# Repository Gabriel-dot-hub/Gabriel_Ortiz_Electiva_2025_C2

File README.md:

# Gabriel_Ortiz_Electiva_2025_C2
Repositorio para las clases de la electiva con el profesor Carlos Antonio Pichardo Viuque

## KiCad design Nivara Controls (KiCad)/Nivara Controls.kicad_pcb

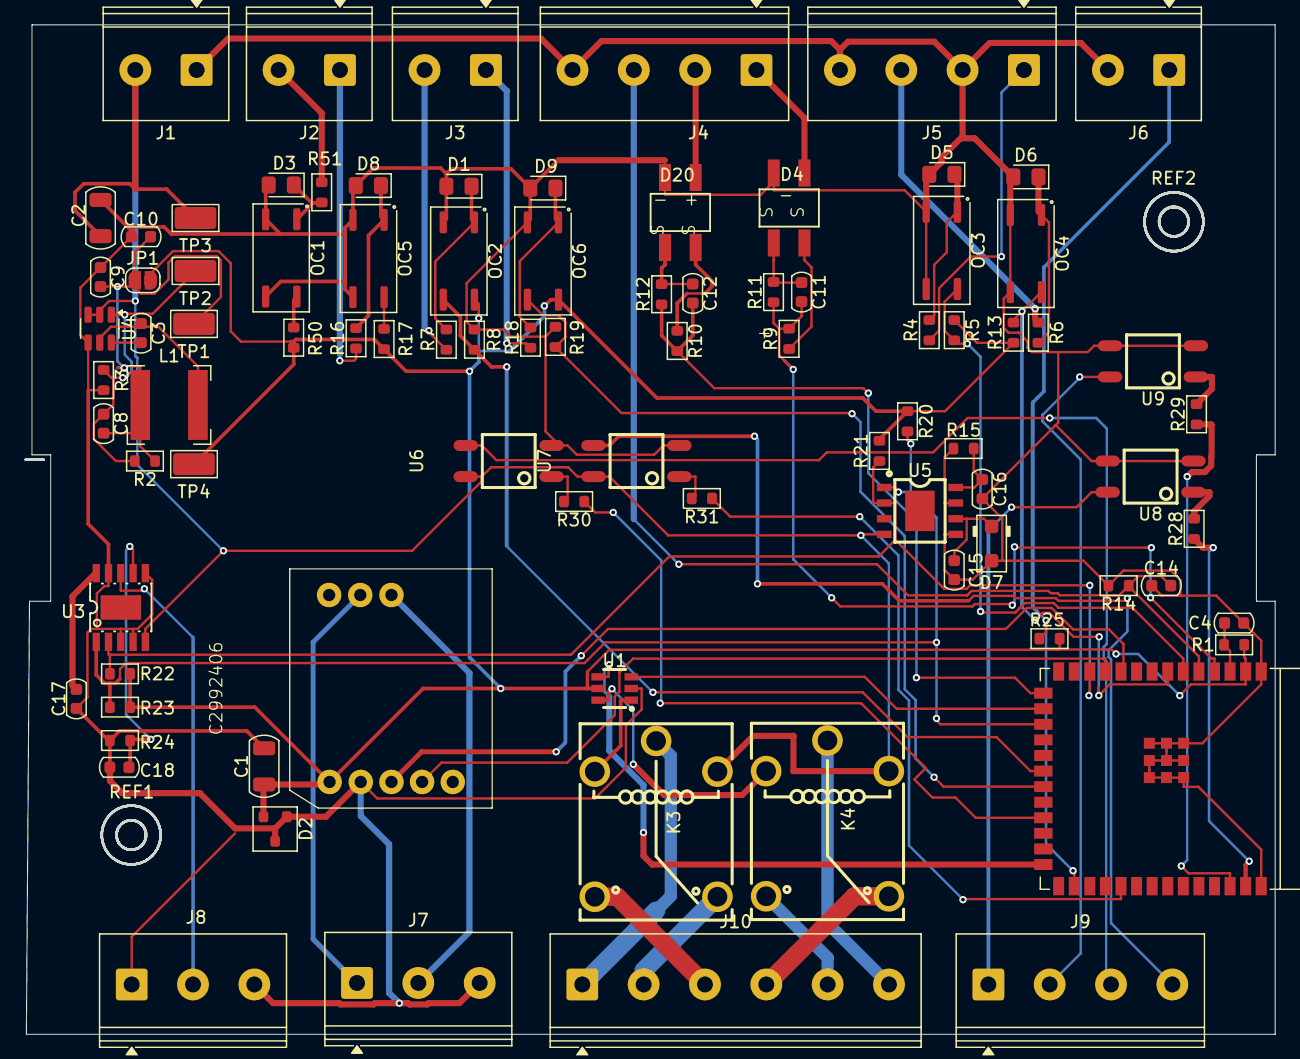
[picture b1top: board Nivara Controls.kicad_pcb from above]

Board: 2 copper layers, 101.8 x 82.3 mm, 91 parts (0 on the bottom side), 70 nets.

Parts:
C1, C2: C_1206; C_1206_3216Metric
C3, C4, C8, C9, C10, C11, C12, C14, C15, C16, C17, C18: C_0603; C_0603_1608Metric
C2992406: C2992406
D1, D3, D5, D6, D8, D9: DL4007; D_0805_2012Metric_Pad1.15x1.40mm_HandSolder
D2: SM712; SOT-23
D4, D20: MB24F_C7427849; MBF-SMD_L4.7-W3.8-P2.50-LS6.8-BL
D7: SMF24A; D_SOD-123F
J1, J2, J3, J6: Screw_Terminal_2_P5.00mm; TerminalBlock_Phoenix_PT-1,5-2-5.0-H_1x02_P5.00mm_Horizontal
J4, J5, J9: Screw_Terminal_4_P5.00mm; TerminalBlock_Phoenix_PT-1,5-4-5.0-H_1x04_P5.00mm_Horizontal
J7, J8: Screw_Terminal_3_P5.00mm; TerminalBlock_Phoenix_PT-1,5-3-5.0-H_1x03_P5.00mm_Horizontal
J10: Screw_Terminal_6_P5.00mm; TerminalBlock_Phoenix_PT-1,5-6-5.0-H_1x06_P5.00mm_Horizontal
JP1: SolderJumper_2_Open; SolderJumper-2_P1.3mm_Open_RoundedPad1.0x1.5mm
K3, K4: SRA-24VDC-CL; RELAY-TH_SRA-X-CX
L1: L_Iron; L_Bourns-SRN6028
OC1, OC2, OC3, OC4, OC5, OC6: LTV-357T-B; SO-4_4.4x3.9mm_P2.54mm
R1, R2, R3, R4, R5, R6, R7, R8, R9, R10, R11, R12, R13, R14, R15, R16, R17, R18, R19, R20, R21, R22, R23, R24, R25, R28, R29, R30, R31, R50, R51: R_0603; R_0603_1608Metric
REF1, REF2: MountingHole_2.5mm
TP1, TP2, TP3, TP4: TestPoint; TestPoint_Keystone_5015_Micro_Mini
U1: LK1802
U2: ESP32-S3-WROOM-1
U3: GP8303-TC50-EW; ESOP-10_L4.9-W3.9-P1.00-LS6.1-BL-EP
U4: AP63203WU; TSOT-23-6
U5: GP8201S-TC50-EW; GP8303-TC50-EW
U6, U7, U8, U9: GAQY211G2S; GAQY211G2s

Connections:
+3.3V: C1.1, C2992406.1 (VCC), D2.2 (A2), JP1.2 (B), OC2.4, OC6.4, R1.1, R5.1, R13.1, R17.1, R20.2, R21.2, R22.2, R23.2, R25.1, R50.1, TP4.1, U1.5 (COM), U2.2 (3V3)
/Board_NIVARA/0mA__10mA_module/SCLK: R20.1, R23.1, U2.17 (GPIO9/TOUCH9/ADC1_CH8/FSPIHD/SUBSPIHD), U3.1 (SLCK), U5.1 (SCLK)
/Board_NIVARA/0mA__10mA_module/SDA: R21.1, R22.1, U2.12 (GPIO8/TOUCH8/ADC1_CH7/SUBSPICS1), U3.2 (SDA), U5.2 (SDA)
/Board_NIVARA/0v__10v_Module/D_0v__10v: C11.2, R9.2, R11.1, U2.4 (GPIO4/TOUCH4/ADC1_CH3)
/Board_NIVARA/0v__32v__module/D_0v__32v__: C12.2, R10.2, R12.1, U2.15 (GPIO3/TOUCH3/ADC1_CH2)
/Board_NIVARA/+Digit_input_1_+: J5.1, R4.1
/Board_NIVARA/+Digit_input_2_+: J5.3, R6.1
/Board_NIVARA/Analog_0-10_input_1: D4.3 (C1), J4.1
/Board_NIVARA/Analog_0-32_input_1: D20.3 (C1), J4.2
/Board_NIVARA/Analog_0_10_OUT_1: C15.2, D7.1 (K), U5.6 (VOUT)
/Board_NIVARA/Analog_4-20_input_1: C14.2, J4.3, R14.1, U2.5 (GPIO5/TOUCH5/ADC1_CH4)
/Board_NIVARA/Analog_4_20_OUT_1: J8.2, U3.8 (IOUT)
/Board_NIVARA/Digit_module/Digit_input1_--: OC3.4, R5.2, U2.6 (GPIO6/TOUCH6/ADC1_CH5)
/Board_NIVARA/Digit_module/Digit_input_2--: OC4.4, R13.2, U2.7 (GPIO7/TOUCH7/ADC1_CH6)
/Board_NIVARA/Driver_RS485/UART_IN: C2992406.3 (TXD), U2.10 (GPIO17/U1TXD/ADC2_CH6)
/Board_NIVARA/Driver_RS485/UART_OUT: C2992406.4 (RXD), U2.11 (GPIO18/U1RXD/ADC2_CH7/CLK_OUT3)
/Board_NIVARA/Input_NPN/NPN-Digit_input_1: OC1.4, R50.2
/Board_NIVARA/Input_NPN/NPN-Digit_input_2: OC5.4, R17.2
/Board_NIVARA/Input_PNP/PNP_Digit_1: OC2.3, R8.1, U2.20 (GPIO12/TOUCH12/ADC2_CH1/FSPICLK/FSPIIO6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)
/Board_NIVARA/Input_PNP/PNP_Digit_2: OC6.3, R19.1, U2.21 (GPIO13/TOUCH13/ADC2_CH2/FSPIQ/FSPIIO7/S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)
/Board_NIVARA/NPN_OUT_1: J9.1, U8.4
/Board_NIVARA/NPN_OUT_2: J9.2, U9.4
/Board_NIVARA/NPN_input_1: J2.2, R51.1
/Board_NIVARA/NPN_input_2: J2.1, R16.1
/Board_NIVARA/Output_NPN/NPN_Input_1: R29.1, U2.38 (GPIO2/TOUCH2/ADC1_CH1)
/Board_NIVARA/Output_NPN/NPN_input_0: R28.1, U2.39 (GPIO1/TOUCH1/ADC1_CH0)
/Board_NIVARA/Output_PNP/PNP_input_0: R30.1, U2.23 (GPIO21)
/Board_NIVARA/Output_PNP/PNP_input_1: R31.1, U2.31 (GPIO38/FSPIWP/SUBSPIWP)
/Board_NIVARA/PNP_OUT_1: J9.3, U6.3
/Board_NIVARA/PNP_OUT_2: J9.4, U7.3
/Board_NIVARA/PNP_input_1: J3.2, R7.1
/Board_NIVARA/PNP_input_2: J3.1, R18.1
/Board_NIVARA/RLY_1_COM: J10.2, K3.2
/Board_NIVARA/RLY_1_NC: J10.1, K3.5
/Board_NIVARA/RLY_1_NO: J10.3, K3.1
/Board_NIVARA/RLY_2_COM: J10.5, K4.1
/Board_NIVARA/RLY_2_NC: J10.4, K4.2
/Board_NIVARA/RLY_2_NO: J10.6, K4.5
/Board_NIVARA/RLY_MODULE/ON_RLY_1: U1.3 (1B), U2.16 (GPIO46)
/Board_NIVARA/RLY_MODULE/ON_RLY_2: U1.4 (2B), U2.26 (GPIO45)
/Board_NIVARA/RS485-A: C2992406.9 (A), J7.1
/Board_NIVARA/RS485-B: C2992406.8 (B), J7.2
/Board_NIVARA/RUN/STOP: J6.1, R25.2, U2.28 (SPIIO6/GPIO35/FSPID/SUBSPID)
GND: C1.2, C2.2, C4.2, C9.1, C10.1, C14.1, C15.1, C16.2, C17.1, C18.2, C2992406.2 (GND), D1.2 (A), D2.1 (A1), D2.3 (Com), D3.2 (A), D4.4 (C2), D5.2 (A), D6.2 (A), D7.2 (A), D8.2 (A), D9.2 (A), D20.4 (C2), J1.1, J4.4, J5.2, J5.4, J6.2, J7.3, J8.3, OC1.2, OC1.3, OC2.2, OC3.2, OC3.3, OC4.2, OC4.3, OC5.2, OC5.3, OC6.2, R3.2, R8.2, R14.2, R19.2, R24.1, U1.2 (E), U2.1 (GND), U2.40 (GND), U2.41 (GND), U3.3 (A0), U3.4 (A1), U3.6 (GND), U3.9 (A2), U4.4 (GND), U5.5 (GND), U6.2, U7.2, U8.2, U8.3, U9.2, U9.3
unnamed: D1.1 (K), OC2.1, R7.2
unnamed: D3.1 (K), OC1.1, R51.2
unnamed: D4.2 (+), R9.1
unnamed: C11.1, D4.1 (-), R11.2
unnamed: D5.1 (K), OC3.1, R4.2
unnamed: D6.1 (K), OC4.1, R6.2
unnamed: D8.1 (K), OC5.1, R16.2
unnamed: D9.1 (K), OC6.1, R18.2
unnamed: D20.2 (+), R10.1
unnamed: C12.1, D20.1 (-), R12.2
unnamed: C8.2, C9.2, C10.2, JP1.1 (A), L1.2, R2.1, TP1.1
unnamed: R28.2, U8.1
unnamed: R29.2, U9.1
unnamed: R30.2, U6.1
unnamed: R31.2, U7.1
unnamed: K3.4, U1.1 (1C)
unnamed: K4.4, U1.6 (2C)
unnamed: C4.1, R1.2, U2.3 (EN)
unnamed: C18.1, R24.2, U3.7 (SET)
unnamed: C17.2, U3.10 (V5V)
unnamed: C3.2, U4.6 (BST)
unnamed: C8.1, R2.2, R3.1, TP2.1, U4.1 (FB)
unnamed: C3.1, L1.1, U4.5 (SW)
unnamed: R15.1, U5.7 (SEL)
unnamed: C16.1, R15.2, U5.8 (V5V)
VCC: C2.1, J1.2, K3.3, K4.3, TP3.1, U3.5 (VCC), U4.2 (EN), U4.3 (IN), U5.4 (VCC), U6.4, U7.4

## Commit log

2025-05-17 Test de commit & push
2025-05-17 test rama correcta
2025-05-17 delete
2025-05-17 commit test 1 a main
2025-05-17 test
2025-05-17 test 1
2025-05-17 Funciona?
2025-05-17 read the text inside
2025-05-22 Tarea #1
2025-05-29 Pieza 3D
2025-06-06 Componentes para NIVARA
2025-06-06 Actualización: Pieza con el logo
2025-06-06 Pieza en FreeCAD
2025-06-06 Etiqueta para NIVARA
2025-06-06 Logo
2025-06-06 Doc de requisitos
2025-06-13 NIVARA Controls
2025-06-13 Actualización sobre datos del relay slim 3v
2025-06-13 Actualización
2025-06-25 Investigación sobre MBSE
2025-07-02 Actualization
2025-07-03 Actualización Módulo C2992406
2025-07-09 Actualización_RLAY
2025-07-16 Actualizado
2025-07-16 ACtual
2025-07-26 Esquemático a PCB (ver errores)
2025-07-26 Componentes
2025-07-26 Acutalizado
2025-07-30 Trabajando en PCB
2025-07-31 Backups
2025-08-09 Actualización VCC en el COM de los Relay
2025-08-22 Orden del GIT y bordes redondeados del 3D
2025-08-22 Bordes suaves (FreeCAD)
2025-08-22 Actualizació Orden de componentes
2025-08-22 rutas
